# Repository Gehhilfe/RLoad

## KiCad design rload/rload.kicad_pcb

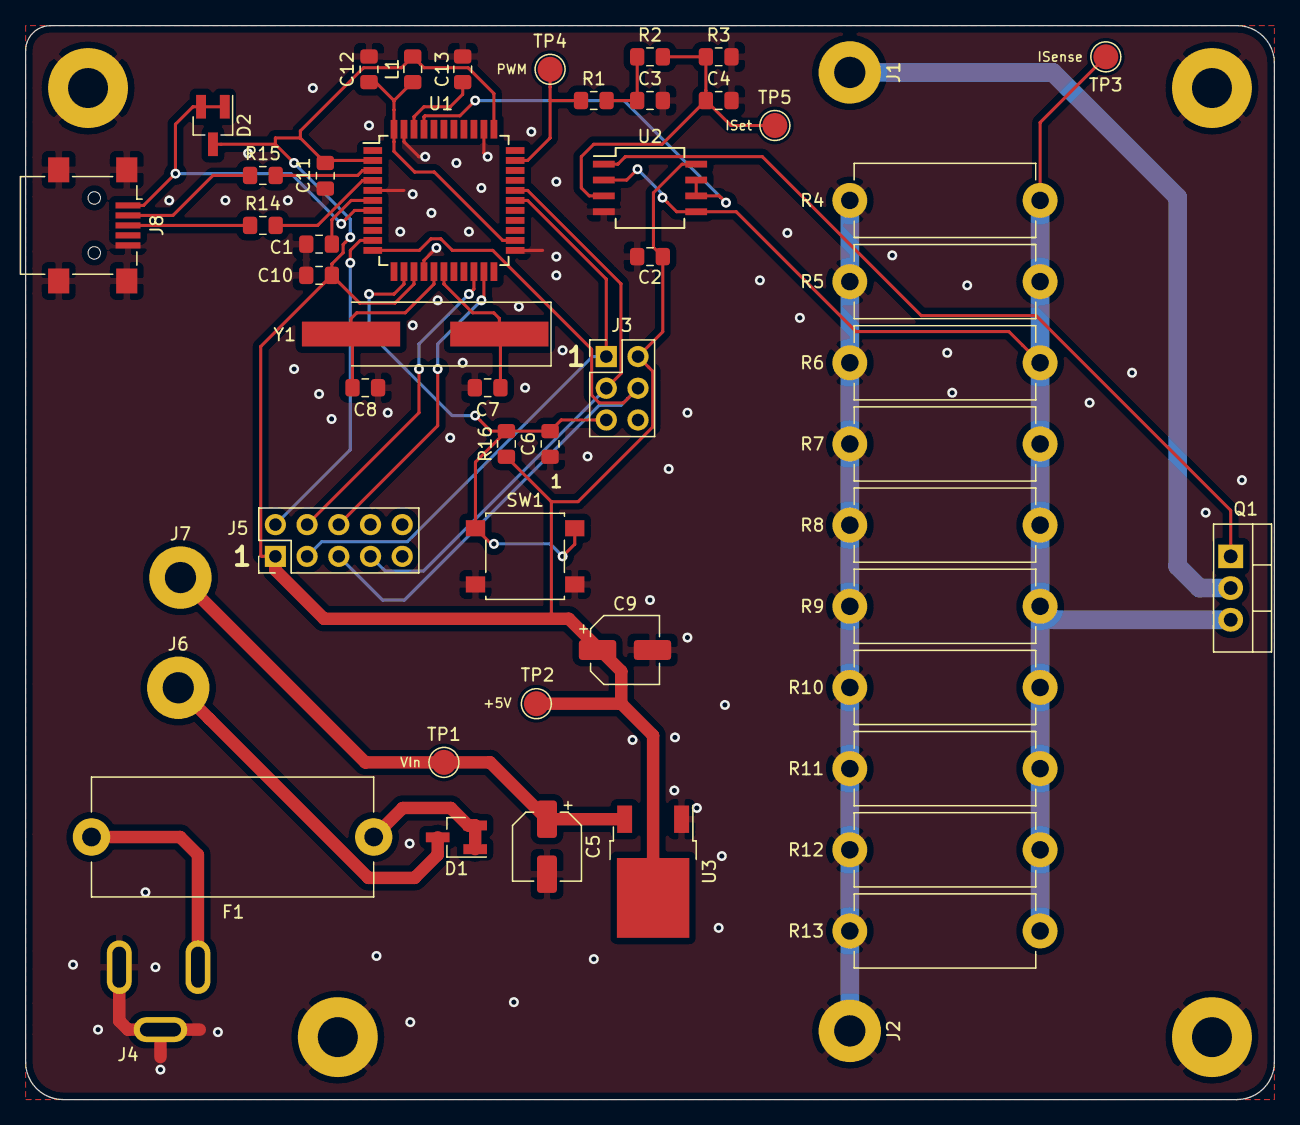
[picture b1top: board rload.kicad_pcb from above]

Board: 2 copper layers, 100.0 x 86.0 mm, 56 parts (1 on the bottom side), 30 nets.

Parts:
C1: 1u; C_0805_2012Metric_Pad1.15x1.40mm_HandSolder
C2, C4, C6, C10, C11, C12, C13: 100n; C_0805_2012Metric_Pad1.15x1.40mm_HandSolder
C3: 10u; C_0805_2012Metric_Pad1.15x1.40mm_HandSolder
C5: 10u; CP_Elec_5x5.8
C7, C8: 22p; C_0805_2012Metric_Pad1.15x1.40mm_HandSolder
C9: 22u; CP_Elec_5x5.8
D1, D2: D_Schottky_AAK; SOT-23_Handsoldering
F1: Fuse; Fuseholder_Cylinder-5x20mm_Stelvio-Kontek_PTF78_Horizontal_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
H1, H2, H3, H4: MountingHole_Pad; MountingHole_3.2mm_M3_Pad
J1, J2, J6, J7: Conn_01x01; MountingHole_2.5mm_Pad
J3: AVR-ISP-6; PinHeader_2x03_P2.54mm_Vertical
J4: Barrel_Jack_Switch; Barrel_Jack_BKL
J5: Conn_02x05_Odd_Even; PinHeader_2x05_P2.54mm_Vertical
J8: USB_B_Micro; USB_Mini-B_Lumberg_2486_01_Horizontal
L1: 10u; L_0805_2012Metric_Pad1.15x1.40mm_HandSolder
Q1: Q_NMOS_GDS; TO-220-3_Vertical
R1: 0.5k; R_0805_2012Metric_Pad1.15x1.40mm_HandSolder
R2, R3: 100k; R_0805_2012Metric_Pad1.15x1.40mm_HandSolder
R4, R5, R6, R7, R8, R9, R10, R11, R12, R13: 10; R_Axial_DIN0614_L14.3mm_D5.7mm_P15.24mm_Horizontal
R14, R15: 22; R_0805_2012Metric_Pad1.15x1.40mm_HandSolder
R16: 10k; R_0805_2012Metric_Pad1.15x1.40mm_HandSolder
SW1: SW_Push; SW_SPST_B3S-1000
TP1: Vin; TestPoint_Pad_D2.0mm
TP2: 5V; TestPoint_Pad_D2.0mm
TP3: ISense; TestPoint_Pad_D2.0mm
TP4: PWM; TestPoint_Pad_D2.0mm
TP5: ISet; TestPoint_Pad_D2.0mm
U1: ATmega32U4-AU; TQFP-44_10x10mm_P0.8mm
U2: Opamp_Dual_Generic; SO-8_5.3x6.2mm_P1.27mm
U3: NCP1117-5.0_TO252; TO-252-2
Y1: 8 Mhz; Crystal_SMD_HC49-SD_HandSoldering

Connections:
+5V: C2.1, C9.1, C10.1, C11.1, D2.3, J3.2, J5.1, L1.2, R16.2, TP2.1, U1.2, U1.14, U1.34, U2.8, U3.2
ADC: U1.41, U2.6, U2.7
AREF: C13.1, U1.42
AVCC: C12.1, L1.1, U1.24, U1.44
CS: J5.2, U1.10
GND: C1.2, C2.2, C3.2, C4.2, C5.2, C6.2, C7.2, C8.2, C9.2, C10.2, C11.2, C12.2, C13.2, H1.1, H2.1, H3.1, H4.1, J2.1, J3.6, J4.2, J4.3, J5.8, J8.5, J8.6, R3.2, R4.1, R5.1, R6.1, R7.1, R8.1, R9.1, R10.1, R11.1, R12.1, R13.1, SW1.2, U1.5, U1.15, U1.23, U1.35, U1.43, U2.4, U3.1
INT_A: J5.4, U1.20
INT_B: J5.6, U1.21
I_SENSE: Q1.3, R4.2, R5.2, R6.2, R7.2, R8.2, R9.2, R10.2, R11.2, R12.2, R13.2, TP3.1, U2.2, U2.5
MISO: J3.1, J5.3, U1.28
MOSI: J3.4, J5.5, U1.11
unnamed: C1.1, U1.6
unnamed: C3.1, R1.1, R2.1
unnamed: C4.1, R2.2, R3.1, TP5.1, U2.3
unnamed: C5.1, J7.1, TP1.1, U3.3
unnamed: C7.1, U1.17, Y1.1
unnamed: C8.1, U1.16, Y1.2
unnamed: D1.1, D1.2, F1.1
unnamed: D1.3, J6.1
unnamed: F1.2, J4.1
unnamed: J1.1, Q1.2
unnamed: J8.2, R15.2
unnamed: J8.3, R14.2
unnamed: Q1.1, U2.1
unnamed: R14.1, U1.4
unnamed: R15.1, U1.3
PWM: R1.2, TP4.1, U1.32
RESET: C6.1, J3.5, R16.1, SW1.1, U1.13
SCK: J3.3, J5.7, U1.29
VBUS: D2.1, D2.2, J8.1, U1.7

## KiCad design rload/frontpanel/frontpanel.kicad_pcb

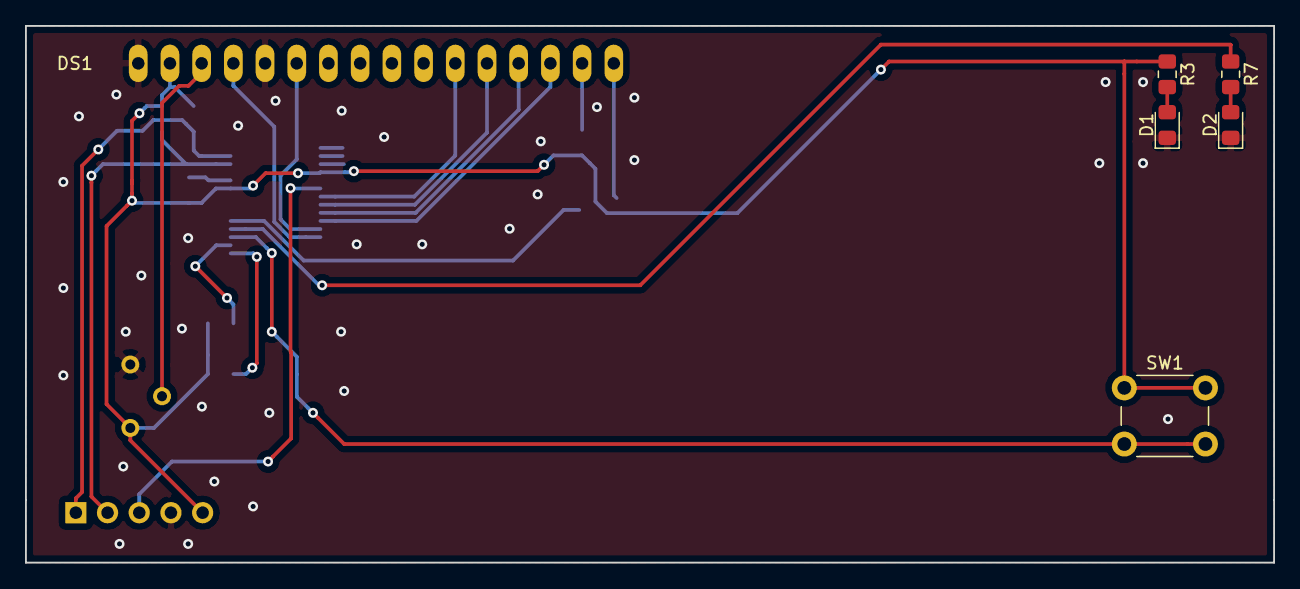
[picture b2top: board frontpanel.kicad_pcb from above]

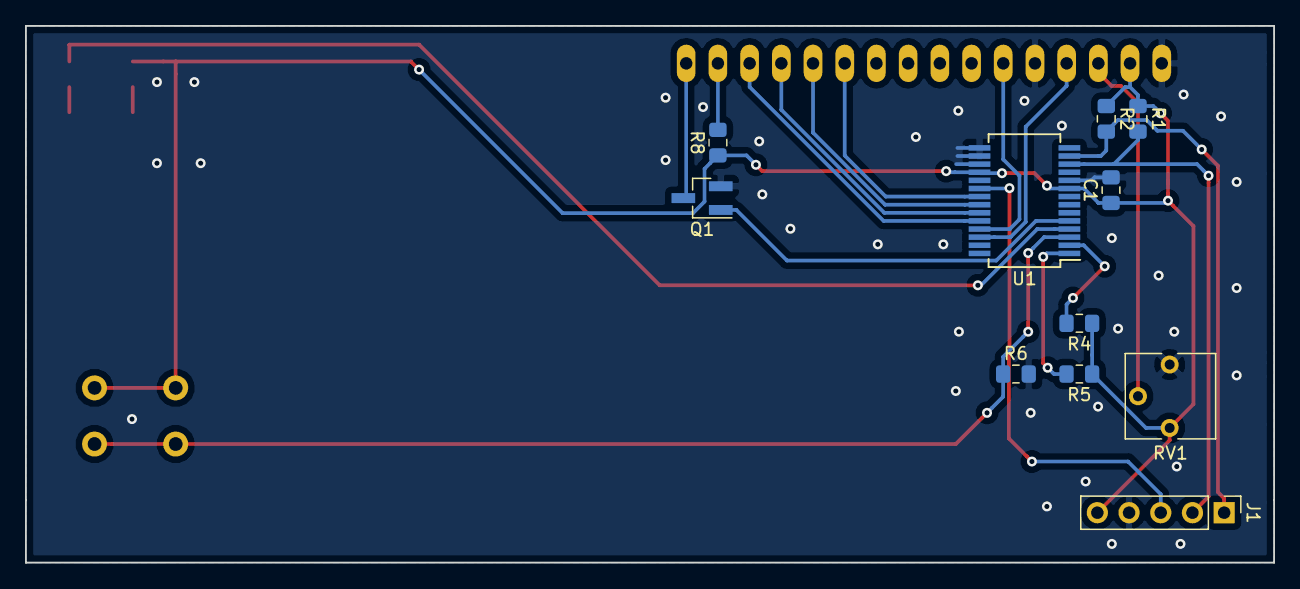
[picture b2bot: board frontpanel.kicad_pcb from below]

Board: 2 copper layers, 100.0 x 43.0 mm, 17 parts (11 on the bottom side), 21 nets.

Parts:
C1: 100n; C_0805_2012Metric_Pad1.15x1.40mm_HandSolder
D1, D2: LED; LED_0805_2012Metric_Pad1.15x1.40mm_HandSolder
DS1: LCD-162C-BL; Display16x2
J1: Conn_01x05_Male; PinHeader_1x05_P2.54mm_Vertical
Q1: Q_NMOS_GSD; SOT-23_Handsoldering
R1, R2, R4, R5, R6: 4K7; R_0805_2012Metric_Pad1.15x1.40mm_HandSolder
R3, R7: 1K; R_0805_2012Metric_Pad1.15x1.40mm_HandSolder
R8: 100; R_0805_2012Metric_Pad1.15x1.40mm_HandSolder
RV1: R_POT 10k; Potentiometer_Vishay_T73YP_Vertical
SW1: SW_Push; SW_PUSH_6mm
U1: MCP23017_SS; SSOP-28_5.3x10.2mm_P0.65mm

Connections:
+5V: C1.1, DS1.2, J1.5, R1.1, R2.1, R3.1, R4.1, R5.1, R8.1, RV1.3, SW1.1, U1.9, U1.18
GND: C1.2, D1.1, D2.1, DS1.1, DS1.5, J1.4, Q1.2, R6.2, RV1.1, U1.10, U1.15, U1.16, U1.17
INTA: J1.3, U1.20
unnamed: D1.2, R3.2
unnamed: D2.2, R7.2
unnamed: DS1.3, RV1.2
unnamed: DS1.15, R8.2
unnamed: DS1.16, Q1.3
PA0: DS1.11, U1.21
PA1: DS1.12, U1.22
PA2: DS1.13, U1.23
PA3: DS1.14, U1.24
PA4: DS1.6, U1.25
PA5: DS1.4, U1.26
PB0: R5.2, U1.1
PB1: R4.2, U1.2
PB2: R6.1, SW1.2, U1.3
PB3: R7.1, U1.4
PB4: Q1.1, U1.5
SCK: J1.2, R1.2, U1.12
SDA: J1.1, R2.2, U1.13

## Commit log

2019-03-17 Create LICENSE
2019-03-17 Project cleanup
2019-03-18 Add python script to generate a svg of a pcb
